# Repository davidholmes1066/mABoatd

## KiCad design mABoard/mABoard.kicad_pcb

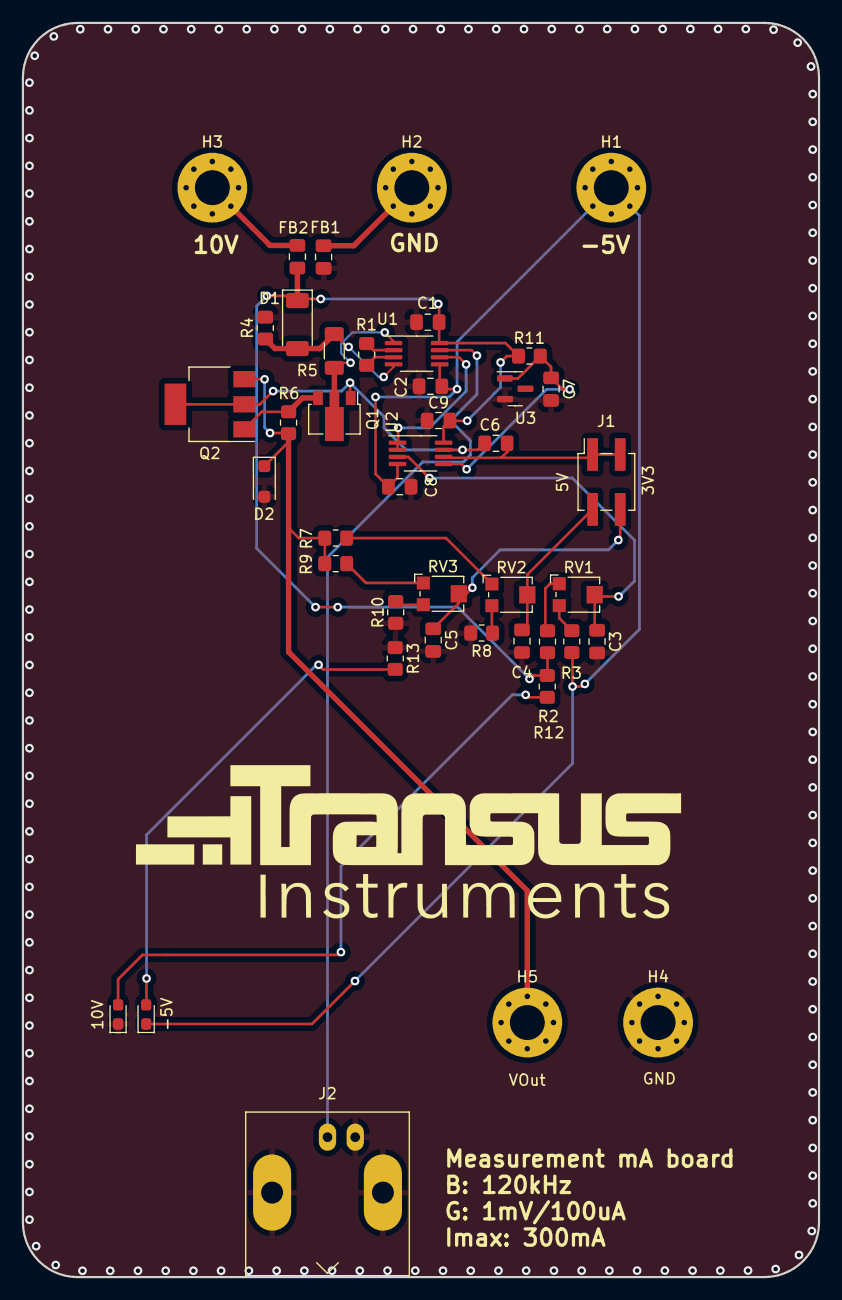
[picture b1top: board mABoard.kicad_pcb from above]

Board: 2 copper layers, 73.0 x 115.0 mm, 43 parts (0 on the bottom side), 27 nets.

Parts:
C1, C2, C3, C4, C5, C7, C8, C9: 0.1uF; C_0805_2012Metric_Pad1.18x1.45mm_HandSolder
C6: 1nF; C_0805_2012Metric_Pad1.18x1.45mm_HandSolder
D1: PDZVTFTR2.0B; D_SOD-128
D2: BZD27C5V1P-E3-08; D_SOD-123F
D3, D4: Green; LED_0603_1608Metric_Pad1.05x0.95mm_HandSolder
FB1, FB2: FB; C_0805_2012Metric_Pad1.18x1.45mm_HandSolder
H1, H2, H3, H4, H5: MH; MountingHole_3.2mm_M3_Pad_Via
J1: Header2.54mm; PinSocket_2x02_P2.54mm_Vertical_SMD
J2: Conn_Coaxial; BNC_Amphenol_B6252HB-NPP3G-50_Horizontal
Q1: PBSS4032NX,115; SOT-89-3
Q2: BCP54TA; SOT-223-3_TabPin2
R1: 200R; R_0805_2012Metric_Pad1.20x1.40mm_HandSolder
R2: 2Meg; R_0805_2012Metric_Pad1.20x1.40mm_HandSolder
R3, R7, R8: 1Meg; R_0805_2012Metric_Pad1.20x1.40mm_HandSolder
R4: 180R 500mW; R_0805_2012Metric_Pad1.20x1.40mm_HandSolder
R5: 1R; R_1206_3216Metric_Pad1.30x1.75mm_HandSolder
R6: 2R 250mW; R_0805_2012Metric_Pad1.20x1.40mm_HandSolder
R9: 2M4; R_0805_2012Metric_Pad1.20x1.40mm_HandSolder
R10: 7M5; R_0805_2012Metric_Pad1.20x1.40mm_HandSolder
R11: 10k; R_0805_2012Metric_Pad1.20x1.40mm_HandSolder
R12: 390R 250mW; R_0805_2012Metric_Pad1.20x1.40mm_HandSolder
R13: 150R; R_0805_2012Metric_Pad1.20x1.40mm_HandSolder
RV1: 20k; Potentiometer_Bourns_TC33X_Vertical
RV2, RV3: 100k; Potentiometer_Bourns_TC33X_Vertical
U1: AD8422; MSOP-8_3x3mm_P0.65mm
U2: ADA4661-2ARMZ; MSOP-8_3x3mm_P0.65mm
U3: LM4040DBZ-2.5; SOT-23

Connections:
+10V: C1.1, C9.1, D1.1 (K), FB2.2, R2.1, R11.1, R12.1, U1.8 (Vs+), U2.8 (V+)
-5V: C2.1, C8.1, D4.1 (K), H1.1, R3.2, U1.5 (Vs-), U2.4 (V-)
GND: C1.2, C2.2, C3.2, C4.2, C5.2, C7.2, C8.2, C9.2, D2.2 (A), D3.1 (K), FB1.2, H4.1, J2.2 (Ext), R4.2, R8.2, R10.2, R13.1, U3.2 (A)
IOUT: J2.1 (In), U1.7
unnamed: D3.2 (A), R12.2
unnamed: D4.2 (A), R13.2
unnamed: FB1.1, H2.1
unnamed: FB2.1, H3.1
unnamed: C6.2, J1.1, J1.3, U2.6 (-)
unnamed: C4.1, J1.2, RV2.2
unnamed: C5.1, J1.4, RV3.2
unnamed: C6.1, Q1.1 (B), Q2.2 (C), U2.7
unnamed: Q1.3 (E), Q2.1 (B), R6.1
unnamed: R1.1, U1.2 (Rg)
unnamed: R1.2, U1.3 (Rg)
unnamed: R2.2, RV1.1
unnamed: R3.1, RV1.3
unnamed: R7.2, RV2.1
unnamed: R8.1, RV2.3
unnamed: R9.2, RV3.1
unnamed: R10.1, RV3.3
unnamed: U1.6 (Ref), U2.1, U2.2 (-)
unnamed: C3.1, RV1.2, U2.3 (+)
unnamed: C7.1, R11.2, U2.5 (+), U3.1 (K)
V+: D1.2 (A), R4.1, R5.1, U1.4 (+)
V-: Q1.2 (C), R5.2, U1.1 (-)
VOUT: D2.1 (K), H5.1, Q2.3 (E), R6.2, R7.1, R9.1

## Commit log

2023-09-12 Added board and schematic
2023-10-13 finalized design
